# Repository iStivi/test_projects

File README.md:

Eagle project files for breakout and testing boards.

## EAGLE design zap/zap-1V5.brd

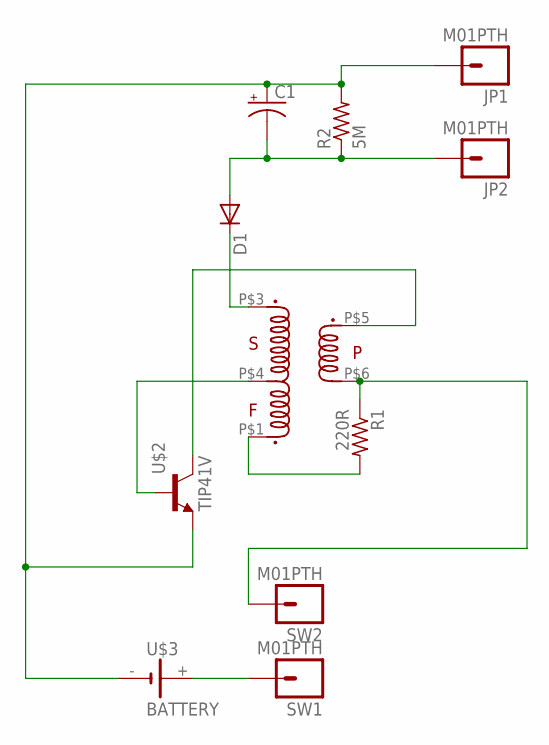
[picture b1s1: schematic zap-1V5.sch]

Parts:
C1: CAPACITOR_POL; E5-10,5-SIDE
D1: DIODEPTH; DIODE-1N4001
JP1, JP2: M01PTH; 1X01
R1: 220R; 0207/2V
R2: 5M; 0207/7
SW1, SW2: M01PTH; 1X01
U$1: XFT-FLYBACK3V; XFT-FLYBACK
U$2: TIP41V; TO220V
U$3: BATTERY; A90

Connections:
unnamed: C1.P$1 (+), JP1.1, R2.2, U$2.3 (E), U$3.-
unnamed: C1.P$2 (-), D1.A, JP2.1, R2.1
unnamed: D1.C, U$1.P$3 (P$1.S)
unnamed: R1.1, SW2.1, U$1.P$6 (P$5.P2)
unnamed: SW1.1, U$3.+
unnamed: R1.2, U$1.P$1 (P$3.F)
unnamed: U$1.P$4 (P$2.CENTRE), U$2.1 (B)
unnamed: U$1.P$5 (P$4.P1), U$2.2 (C)

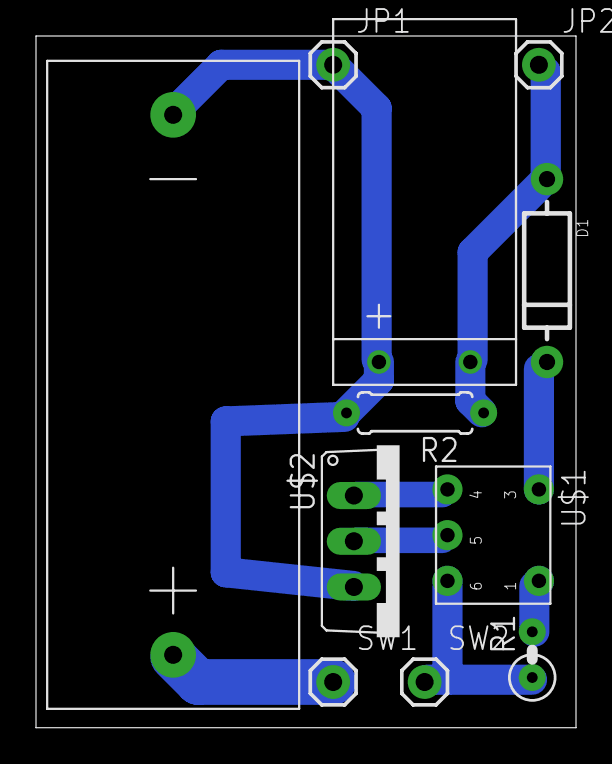
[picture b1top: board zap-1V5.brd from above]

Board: 2 copper layers, 30.0 x 38.4 mm, 11 parts (0 on the bottom side), 8 nets.

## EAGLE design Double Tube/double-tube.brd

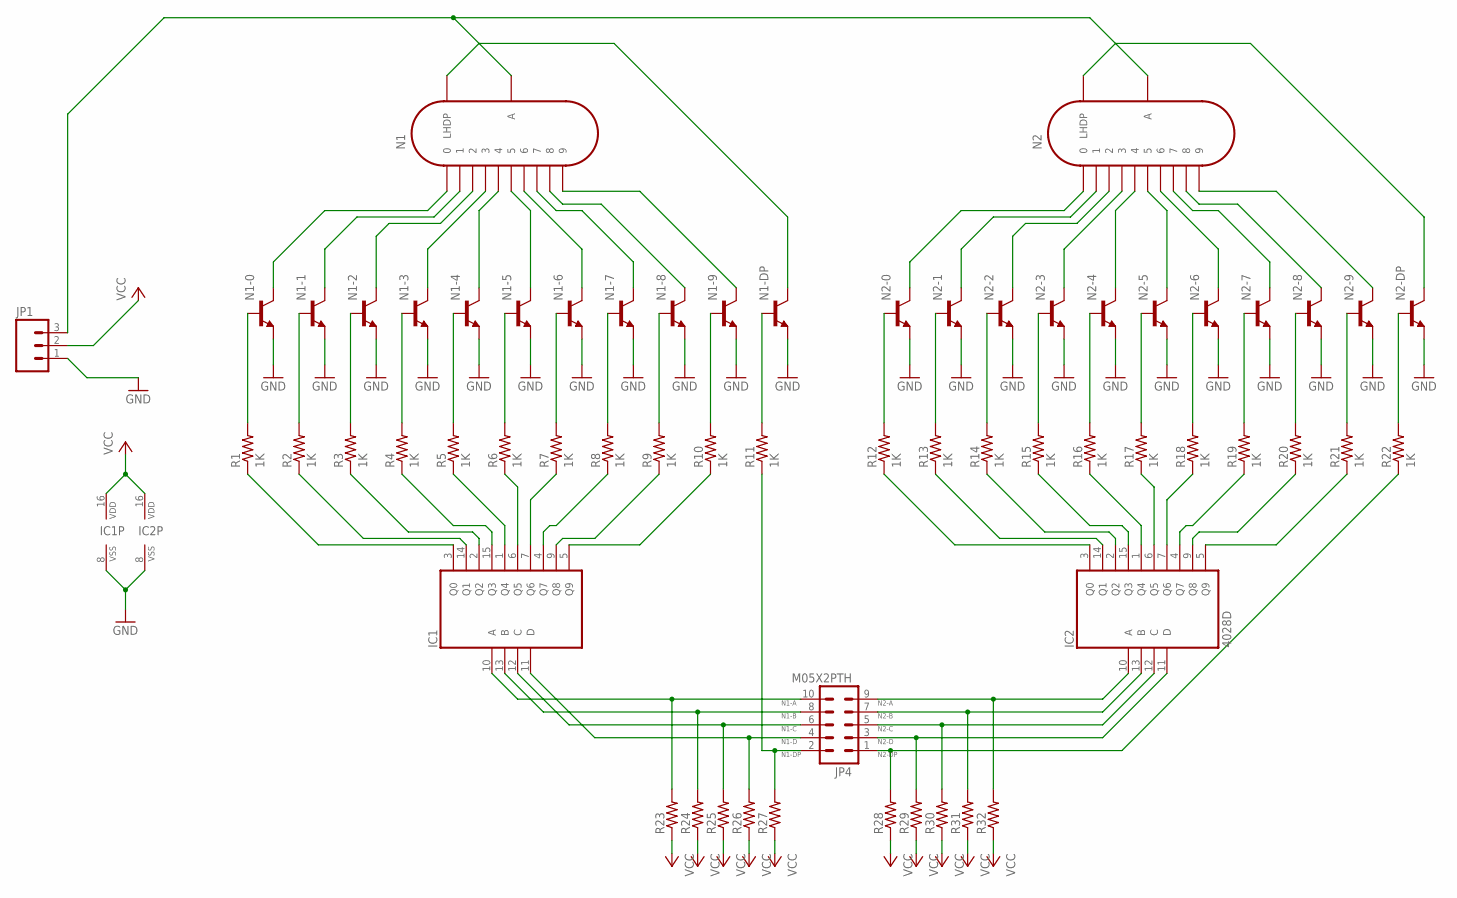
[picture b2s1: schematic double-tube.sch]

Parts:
IC1, IC2: 4028D; SO16
JP1: M03PTH; 1X03
JP4: M05X2PTH; AVR_ICSP
N1, N2: IN-12B; IN-12
N1-0, N1-1, N1-2, N1-3, N1-4, N1-5, N1-6, N1-7, N1-8, N1-9, N1-DP, N2-0, N2-1, N2-2, N2-3, N2-4, N2-5, N2-6, N2-7, N2-8, N2-9, N2-DP: NPN_SMD; SOT-23
R1, R2, R3, R4, R5, R6, R7, R8, R9, R10, R11, R12, R13, R14, R15, R16, R17, R18, R19, R20, R21, R22: 1K; R0603
R23, R24, R25, R26, R27, R28, R29, R30, R31, R32: RESISTORR0603; R0603

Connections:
180V: JP1.3, N1.A, N2.A
N1-A: IC1.10 (A), JP4.10, R23.2
N1-B: IC1.13 (B), JP4.8, R24.2
N1-C: IC1.12 (C), JP4.6, R25.2
N1-D: IC1.11 (D), JP4.4, R26.2
N1-DP: JP4.2, R11.1, R27.2
N2-0: N2.0, N2-0.3 (C)
N2-A: IC2.10 (A), JP4.9, R32.2
N2-B: IC2.13 (B), JP4.7, R31.2
N2-C: IC2.12 (C), JP4.5, R30.2
N2-D: IC2.11 (D), JP4.3, R29.2
N2-DP: JP4.1, R22.1, R28.2
unnamed: N1.0, N1-0.3 (C)
unnamed: N1.1, N1-1.3 (C)
unnamed: N1.2, N1-2.3 (C)
unnamed: N1.3, N1-3.3 (C)
unnamed: N1.4, N1-4.3 (C)
unnamed: N1.9, N1-9.3 (C)
unnamed: N1.8, N1-8.3 (C)
unnamed: N1.7, N1-7.3 (C)
unnamed: N1.6, N1-6.3 (C)
unnamed: N1.5, N1-5.3 (C)
unnamed: N1.LHDP, N1-DP.3 (C)
unnamed: N1-0.1 (B), R1.2
unnamed: N1-1.1 (B), R2.2
unnamed: N1-2.1 (B), R3.2
unnamed: N1-3.1 (B), R4.2
unnamed: N1-4.1 (B), R5.2
unnamed: N1-5.1 (B), R6.2
unnamed: N1-9.1 (B), R10.2
unnamed: N1-6.1 (B), R7.2
unnamed: N1-7.1 (B), R8.2
unnamed: N1-8.1 (B), R9.2
unnamed: IC1.3 (Q0), R1.1
unnamed: IC1.14 (Q1), R2.1
unnamed: N1-DP.1 (B), R11.2
unnamed: IC1.2 (Q2), R3.1
unnamed: N2.1, N2-1.3 (C)
unnamed: N2.2, N2-2.3 (C)
unnamed: N2.3, N2-3.3 (C)
unnamed: N2.4, N2-4.3 (C)
unnamed: N2.9, N2-9.3 (C)
unnamed: N2.8, N2-8.3 (C)
unnamed: N2.7, N2-7.3 (C)
unnamed: N2.6, N2-6.3 (C)
unnamed: N2.5, N2-5.3 (C)
unnamed: N2.LHDP, N2-DP.3 (C)
unnamed: N2-0.1 (B), R12.2
unnamed: N2-1.1 (B), R13.2
unnamed: N2-2.1 (B), R14.2
unnamed: N2-3.1 (B), R15.2
unnamed: N2-4.1 (B), R16.2
unnamed: N2-5.1 (B), R17.2
unnamed: N2-9.1 (B), R21.2
unnamed: N2-6.1 (B), R18.2
unnamed: N2-7.1 (B), R19.2
unnamed: N2-8.1 (B), R20.2
unnamed: IC1.15 (Q3), R4.1
unnamed: N2-DP.1 (B), R22.2
unnamed: IC1.1 (Q4), R5.1
unnamed: IC1.6 (Q5), R6.1
unnamed: IC1.7 (Q6), R7.1
unnamed: IC1.5 (Q9), R10.1
unnamed: IC1.9 (Q8), R9.1
unnamed: IC1.4 (Q7), R8.1
unnamed: IC2.3 (Q0), R12.1
unnamed: IC2.14 (Q1), R13.1
unnamed: IC2.2 (Q2), R14.1
unnamed: IC2.15 (Q3), R15.1
unnamed: IC2.1 (Q4), R16.1
unnamed: IC2.6 (Q5), R17.1
unnamed: IC2.7 (Q6), R18.1
unnamed: IC2.5 (Q9), R21.1
unnamed: IC2.9 (Q8), R20.1
unnamed: IC2.4 (Q7), R19.1

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
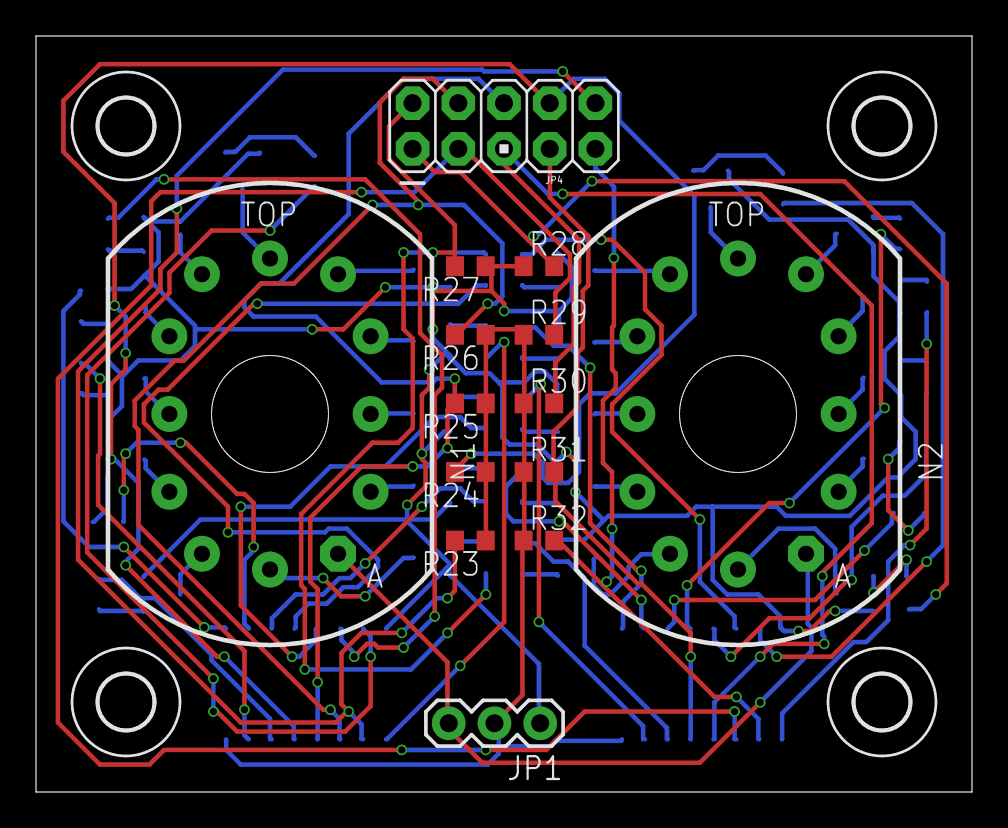
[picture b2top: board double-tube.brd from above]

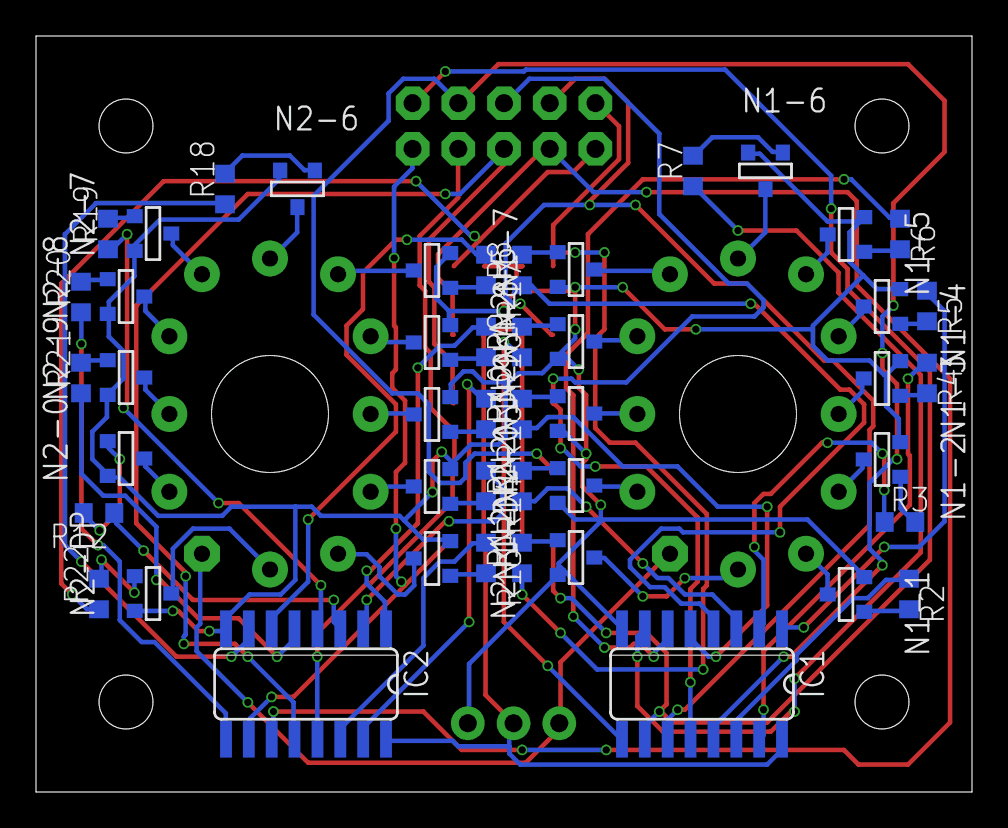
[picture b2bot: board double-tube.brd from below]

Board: 2 copper layers, 52.0 x 42.0 mm, 66 parts (47 on the bottom side), 77 nets.

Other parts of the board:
U$1: BUZZBOY-SILK
U$2, U$3, U$4, U$5: 3,0-SMALL
U$6: BUZZBOY-SILK-BOTTOM

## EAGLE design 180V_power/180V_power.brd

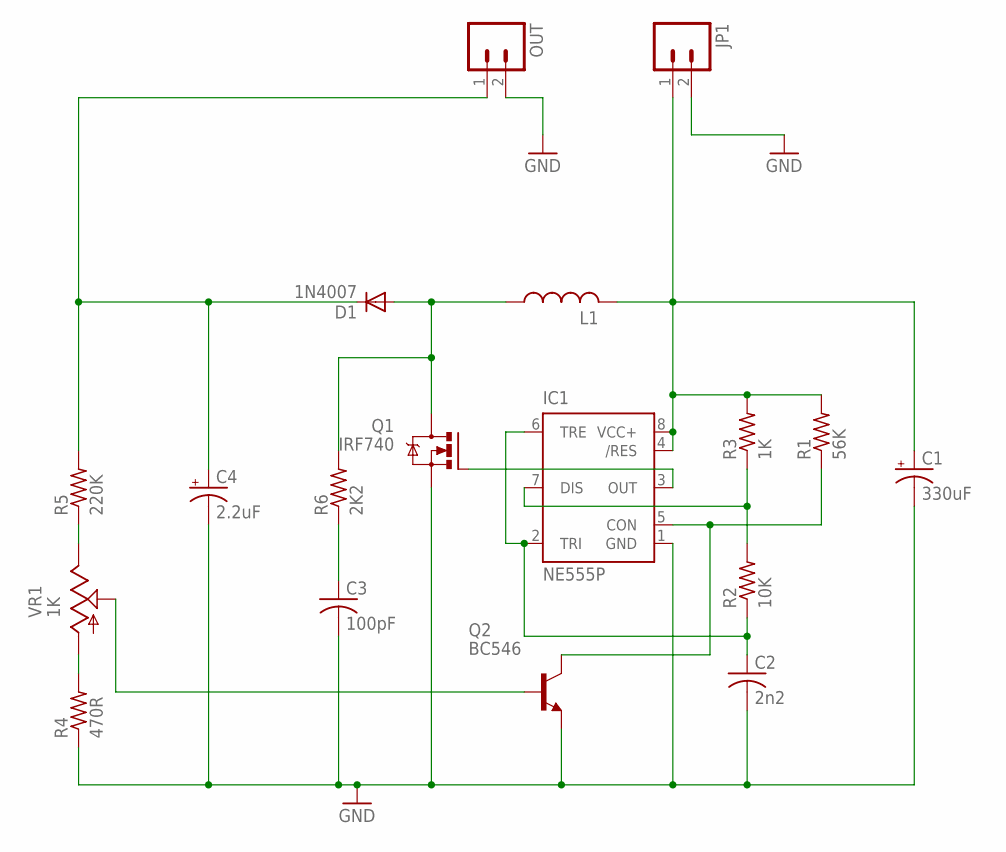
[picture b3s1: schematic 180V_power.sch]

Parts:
C1: 330uF; E5-10,5
C2: 2n2; C050-025X075
C3: 100pF; C050-025X075
C4: 2.2uF; E3,5-8
D1: 1N4007; DIODE-1N4001
IC1: NE555P; DIL08
JP1: M023.5MM; SCREWTERMINAL-3.5MM-2
L1: INDUCTOR; RBL0712
OUT: M023.5MM; SCREWTERMINAL-3.5MM-2
Q1: IRF740; TO220BV
Q2: BC546; TO92-EBC
R1: 56K; 0207/10
R2: 10K; 0207/10
R3: 1K; 0207/10
R4: 470R; 0207/10
R5: 220K; 0207/10
R6: 2K2; 0207/10
VR1: 1K; CA6V

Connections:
GND: C1.-, C2.2, C3.2, C4.-, IC1.1 (GND), JP1.2, OUT.2, Q1.S, Q2.E, R4.1
unnamed: IC1.3 (OUT), Q1.G
unnamed: C3.1, R6.1
unnamed: IC1.5 (CON), Q2.C, R1.1
unnamed: IC1.7 (DIS), R2.2, R3.1
unnamed: C2.1, IC1.2 (TRI), IC1.6 (TRE), R2.1
unnamed: D1.A, L1.P$1 (1), Q1.D, R6.2
unnamed: C4.+, D1.C, OUT.1, R5.2
unnamed: R5.1, VR1.E
unnamed: R4.2, VR1.A
unnamed: Q2.B, VR1.S
unnamed: C1.+, IC1.4 (/RES), IC1.8 (VCC+), JP1.1, L1.P$2 (2), R1.2, R3.2

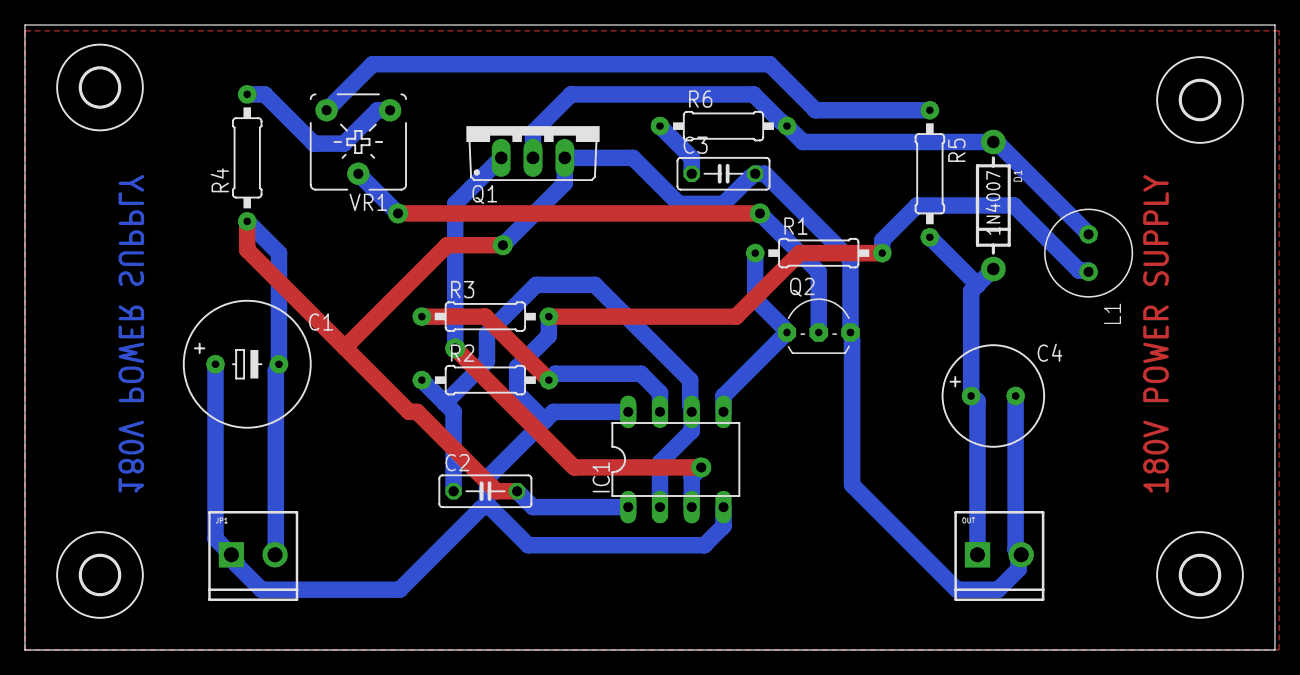
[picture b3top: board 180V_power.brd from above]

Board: 2 copper layers, 100.0 x 50.0 mm, 22 parts (0 on the bottom side), 12 nets.

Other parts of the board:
U$1, U$2, U$3, U$4: 3,0

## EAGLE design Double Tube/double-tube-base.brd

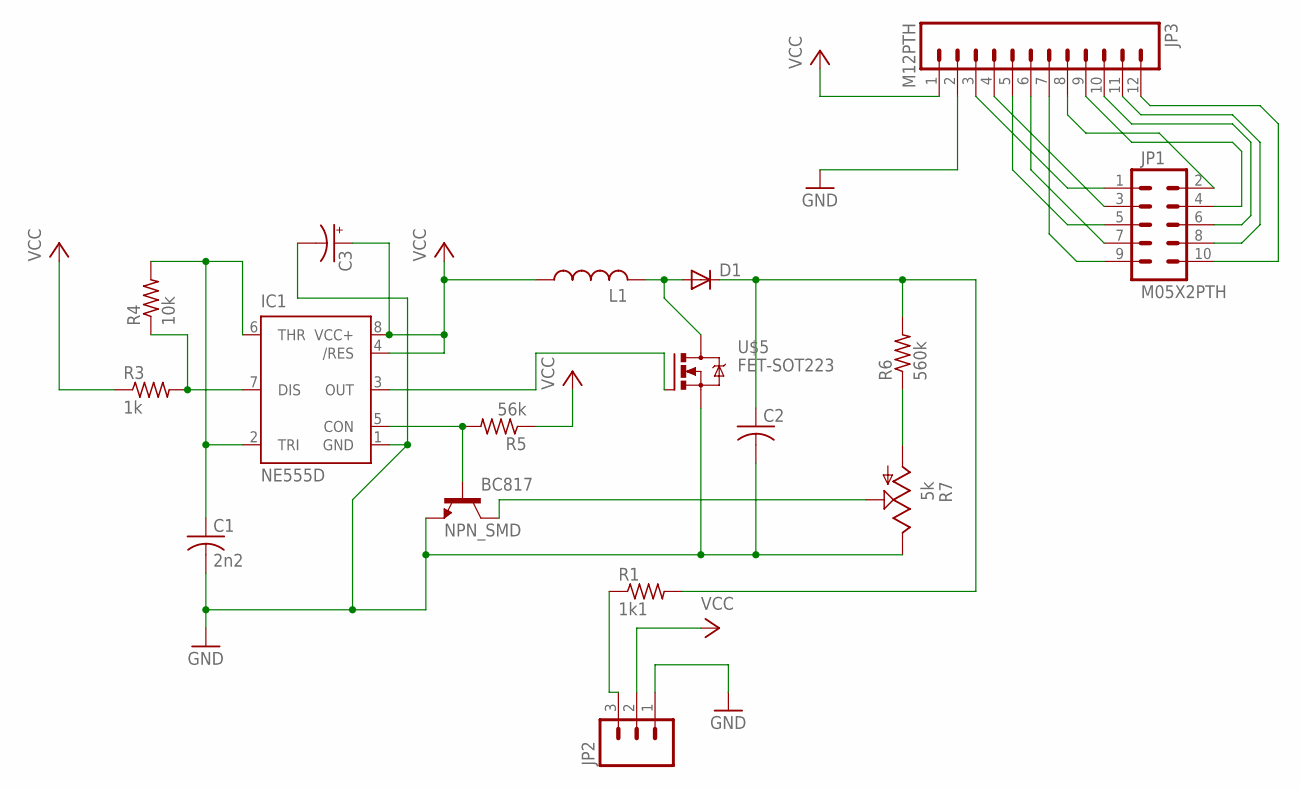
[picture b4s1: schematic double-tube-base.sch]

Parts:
BC817: NPN_SMD; SOT-23
C1: 2n2; C0603K
C2: CAPACITORC1812K; C1812K
C3: CAPACITOR_POLSMCD; SMC_D
D1: DIODESMA; SMA-DIODE
IC1: NE555D; SO08
JP1: M05X2PTH; AVR_ICSP
JP2: M03PTH; 1X03
JP3: M12PTH; 1X12
L1: INDUCTORSMD-10MM; SMD-10MM
R1: 1k1; R1206
R3: 1k; R0603
R4: 10k; R0603
R5: 56k; R0603
R6: 560k; R1206
R7: 5k; TRIM-EVM2N
U$5: FET-SOT223; SOT-223

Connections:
GND: BC817.2 (E), C1.2, C2.2, C3.-, IC1.1 (GND), JP2.1, JP3.2, R7.P$3 (E), U$5.3 (S)
unnamed: IC1.7 (DIS), R3.2, R4.1
unnamed: C1.1, IC1.2 (TRI), IC1.6 (THR), R4.2
unnamed: BC817.1 (B), IC1.5 (CON), R5.2
unnamed: D1.A, L1.P$2 (2), U$5.2 (D), U$5.4 (D)
unnamed: C2.1, D1.C, R1.2, R6.2
unnamed: BC817.3 (C), R7.P$2 (S)
unnamed: R6.1, R7.P$1 (A)
unnamed: IC1.3 (OUT), U$5.1 (G)
unnamed: JP2.3, R1.1
unnamed: JP1.1, JP3.3
unnamed: JP1.3, JP3.4
unnamed: JP1.5, JP3.5
unnamed: JP1.7, JP3.6
unnamed: JP1.9, JP3.7
unnamed: JP1.2, JP3.8
unnamed: JP1.4, JP3.9
unnamed: JP1.6, JP3.10
unnamed: JP1.8, JP3.11
unnamed: JP1.10, JP3.12
VCC: C3.+, IC1.4 (/RES), IC1.8 (VCC+), JP2.2, JP3.1, L1.P$1 (1), R3.1, R5.1

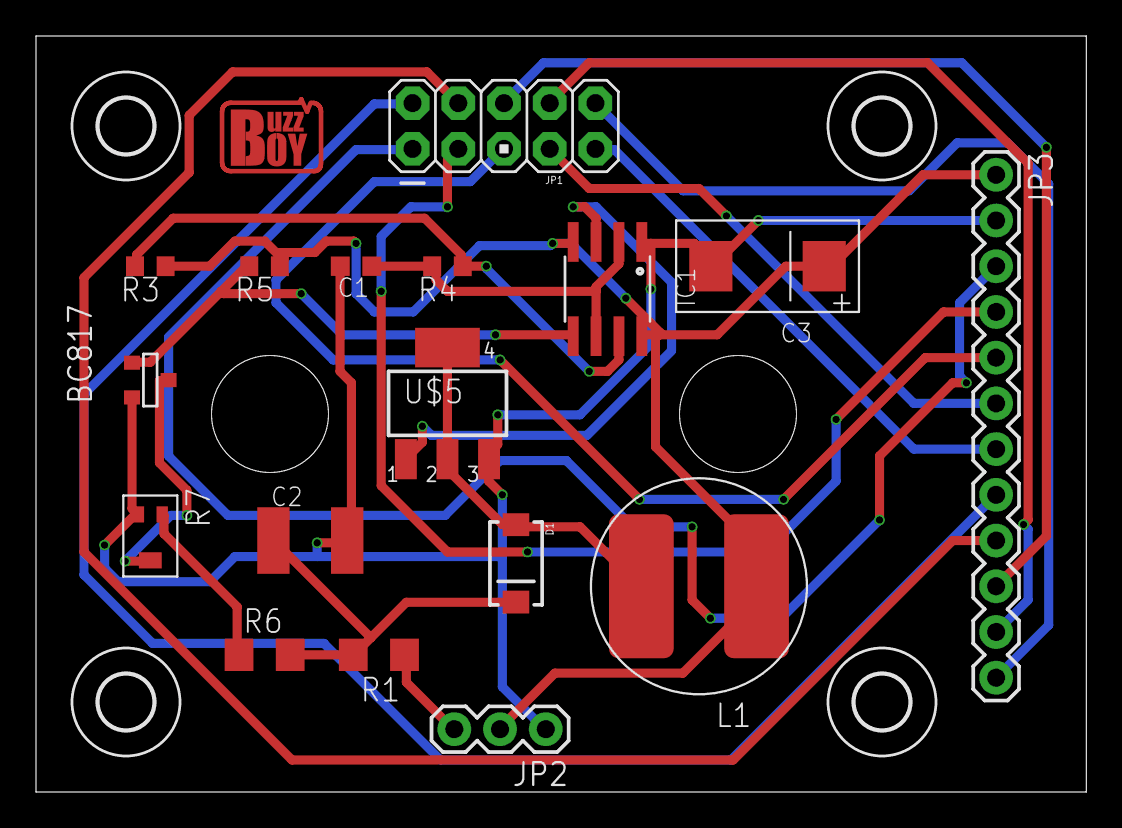
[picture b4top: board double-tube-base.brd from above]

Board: 2 copper layers, 58.4 x 42.0 mm, 23 parts (1 on the bottom side), 21 nets.

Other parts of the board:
U$1, U$2, U$3, U$4: 3,0-SMALL
U$6: BUZZBOY
U$7: BUZZBOY-SILK-BOTTOM

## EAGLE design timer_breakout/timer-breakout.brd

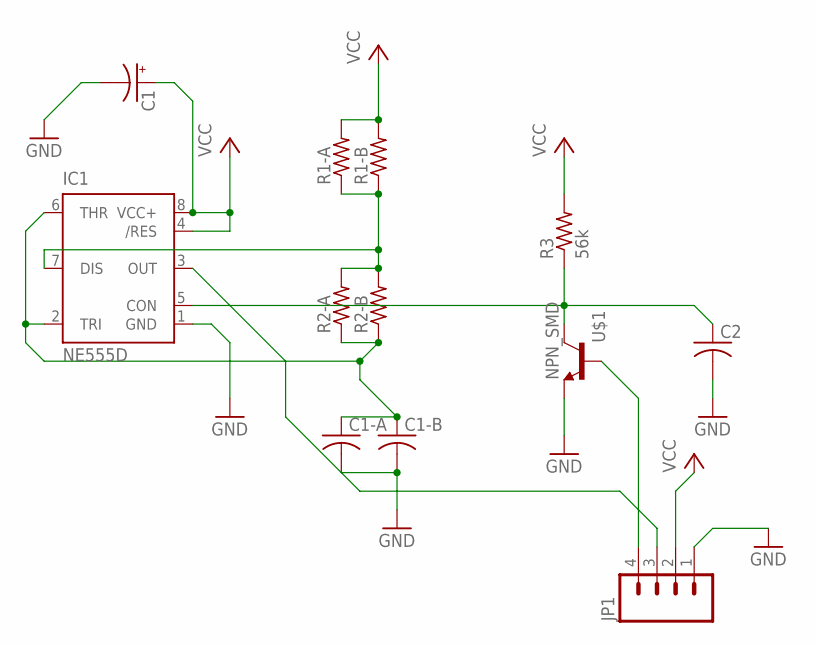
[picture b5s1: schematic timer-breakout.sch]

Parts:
C1: CAPACITOR_POLSMCD; SMC_D
C1-A, C2: CAPACITORC1206K; C1206K
C1-B: CAPACITORC0805K; C0805K
IC1: NE555D; SO08
JP1: M04PTH; 1X04
R1-A, R2-A: RESISTORR1206; R1206
R1-B, R2-B: RESISTORR0805; R0805
R3: 56k; R0805
U$1: NPN_SMD; SOT-23

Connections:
GND: C1.-, C1-A.2, C1-B.2, C2.2, IC1.1 (GND), JP1.1, U$1.2 (E)
unnamed: C1-A.1, C1-B.1, IC1.2 (TRI), IC1.6 (THR), R2-A.1, R2-B.1
unnamed: C2.1, IC1.5 (CON), R3.1, U$1.3 (C)
unnamed: JP1.4, U$1.1 (B)
unnamed: IC1.7 (DIS), R1-A.1, R1-B.1, R2-A.2, R2-B.2
unnamed: IC1.3 (OUT), JP1.3
VCC: C1.+, IC1.4 (/RES), IC1.8 (VCC+), JP1.2, R1-A.2, R1-B.2, R3.2

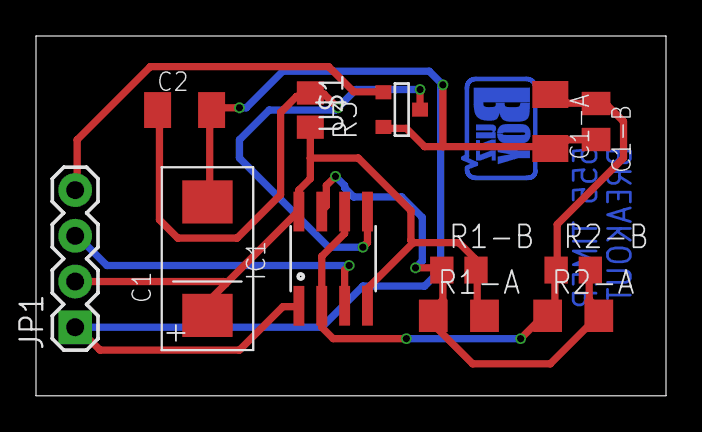
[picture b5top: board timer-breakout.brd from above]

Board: 2 copper layers, 35.0 x 20.0 mm, 14 parts (1 on the bottom side), 7 nets.

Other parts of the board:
U$2: BUZZBOY-SILK
U$3: BUZZBOY

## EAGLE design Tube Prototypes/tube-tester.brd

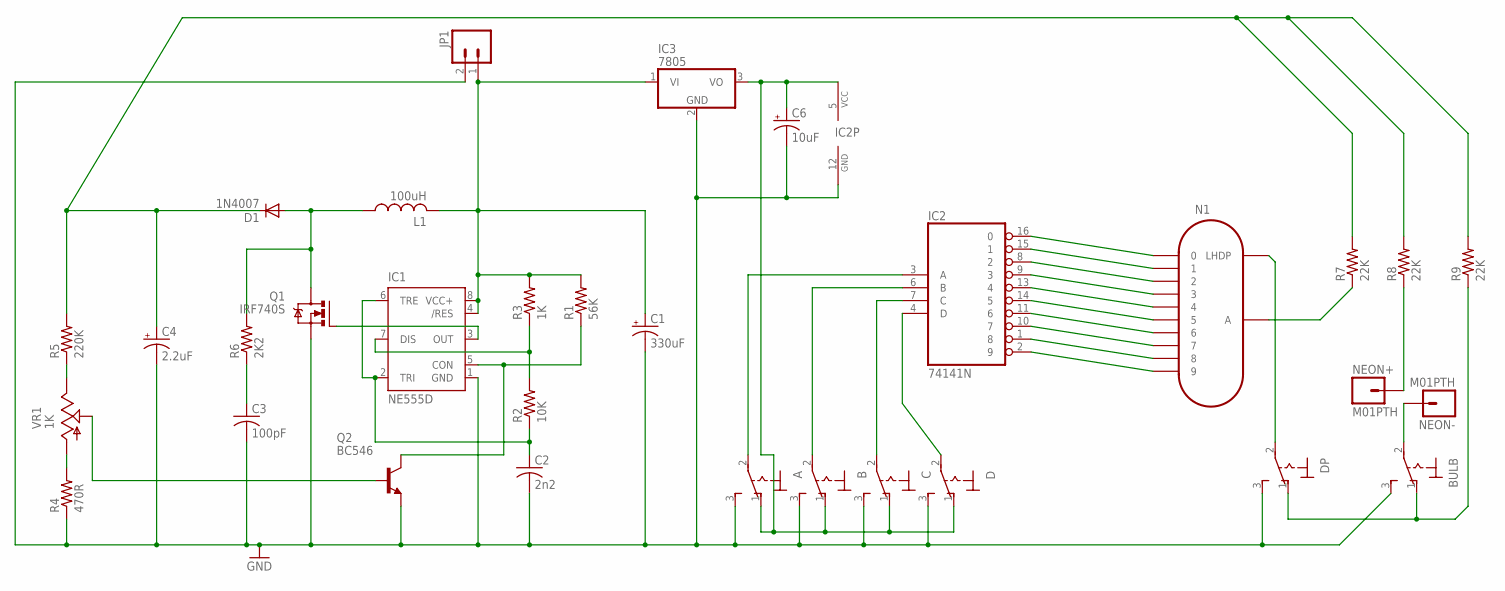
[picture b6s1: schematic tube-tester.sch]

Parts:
A: 320-916
B: 320-916
BULB: 320-916
C: 320-916
C1: 330uF; E5-10,5
C2: 2n2; C1206K
C3: 100pF; C1206K
C4: 2.2uF; E3,5-8
C6: 10uF; E2-5
D: 320-916
D1: 1N4007; SMA-DIODE
DP: 320-916
IC1: NE555D; SO08
IC2: 74141N; DIL16
IC3: 7805; TO220H
JP1: M023.5MM; SCREWTERMINAL-3.5MM-2
L1: 100uH; 0207/10
N1: IN-12B; IN-12
NEON+: M01PTH; 1X01
NEON-: M01PTH; 1X01
Q1: IRF740S; TO263
Q2: BC546; TO92-EBC
R1: 56K; R1206
R2: 10K; R1206
R3: 1K; R1206
R4: 470R; 0207/10
R5: 220K; 0207/10
R6: 2K2; R1206
R7, R8, R9: 22K; 0207/10
VR1: 1K; CA6V

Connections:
GND: A.3 (S), B.3 (S), BULB.3 (S), C.3 (S), C1.-, C2.2, C3.2, C4.-, C6.-, D.3 (S), DP.3 (S), IC1.1 (GND), IC2.12 (GND), IC3.2 (GND), JP1.2, Q1.2 (S), Q2.E, R4.1
unnamed: IC1.3 (OUT), Q1.1 (G)
unnamed: C3.1, R6.1
unnamed: IC1.5 (CON), Q2.C, R1.1
unnamed: IC1.7 (DIS), R2.2, R3.1
unnamed: C2.1, IC1.2 (TRI), IC1.6 (TRE), R2.1
unnamed: D1.A, L1.1, Q1.3 (D), R6.2
unnamed: C4.+, D1.C, R5.2, R7.2, R8.2, R9.2
unnamed: R5.1, VR1.E
unnamed: R4.2, VR1.A
unnamed: Q2.B, VR1.S
unnamed: IC2.15 (1), N1.1
unnamed: IC2.8 (2), N1.2
unnamed: IC2.9 (3), N1.3
unnamed: IC2.13 (4), N1.4
unnamed: IC2.14 (5), N1.5
unnamed: IC2.11 (6), N1.6
unnamed: IC2.10 (7), N1.7
unnamed: IC2.1 (8), N1.8
unnamed: IC2.2 (9), N1.9
unnamed: IC2.16 (0), N1.0
unnamed: N1.A, R7.1
unnamed: A.2, IC2.3 (A)
unnamed: B.2, IC2.6 (B)
unnamed: C.2, IC2.7 (C)
unnamed: D.2, IC2.4 (D)
unnamed: C1.+, IC1.4 (/RES), IC1.8 (VCC+), IC3.1 (VI), JP1.1, L1.2, R1.2, R3.2
unnamed: NEON+.1, R8.1
unnamed: BULB.2, NEON-.1
unnamed: A.1 (O), B.1 (O), C.1 (O), C6.+, D.1 (O), IC2.5 (VCC), IC3.3 (VO)
unnamed: DP.2, N1.LHDP
unnamed: BULB.1 (O), DP.1 (O), R9.1

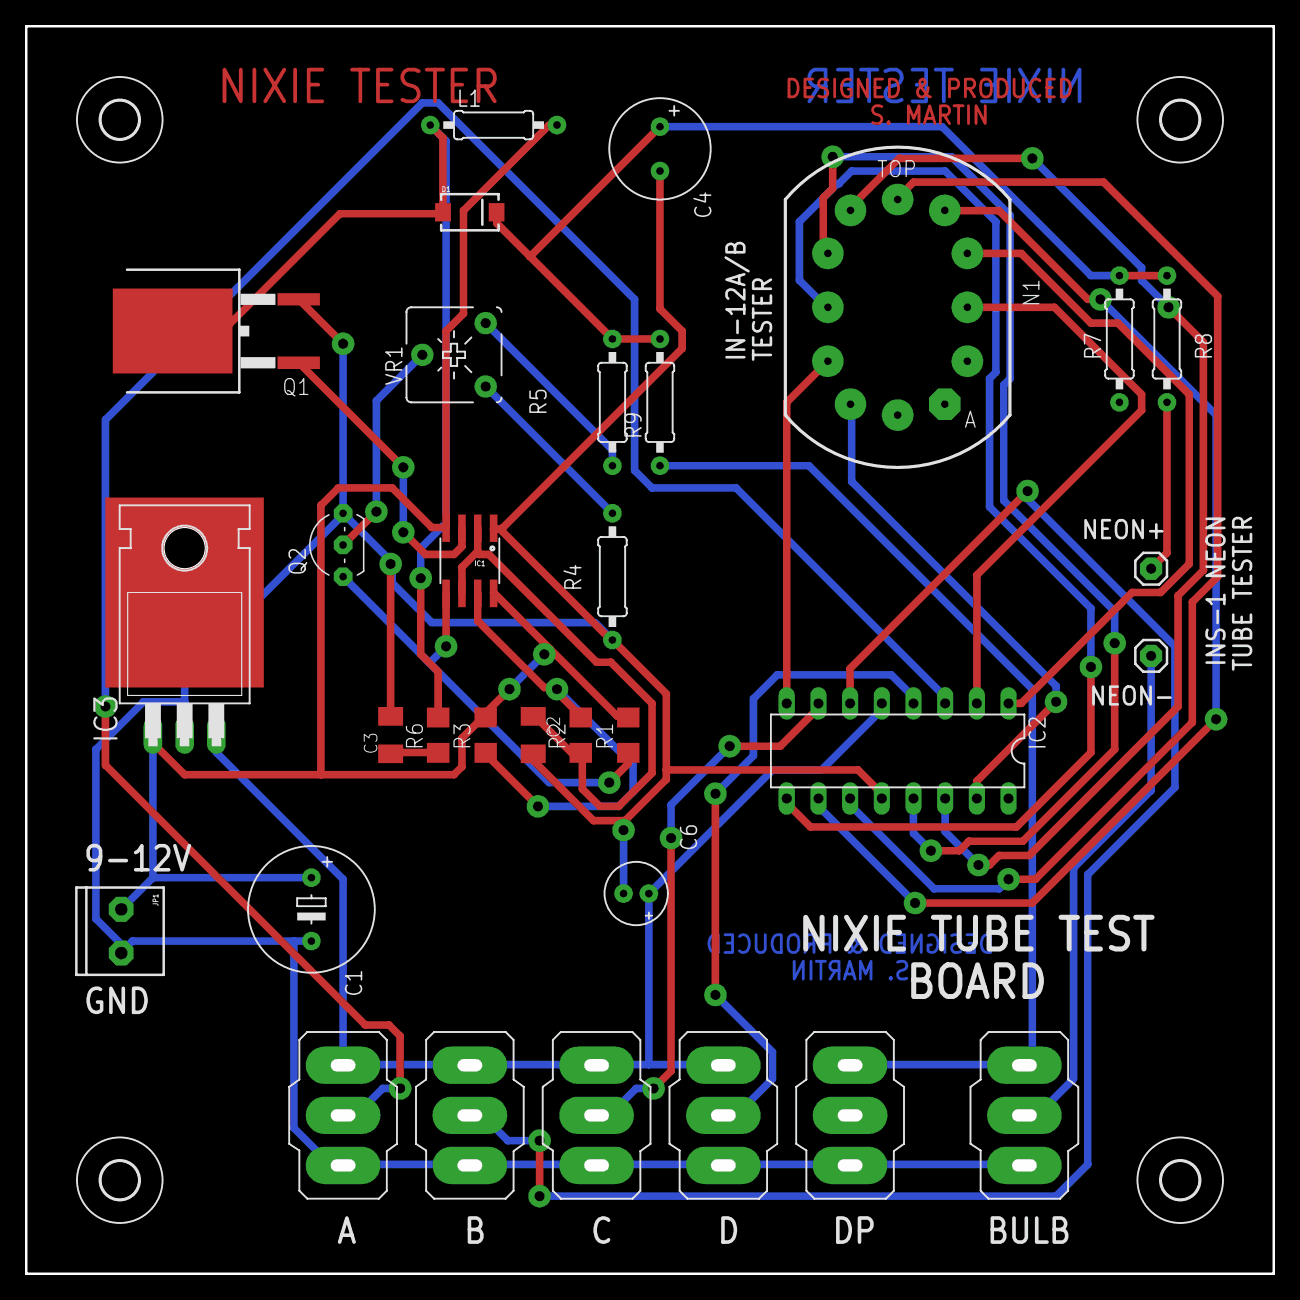
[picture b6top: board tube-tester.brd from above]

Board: 2 copper layers, 100.0 x 100.0 mm, 36 parts (0 on the bottom side), 32 nets.

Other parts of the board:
U$1, U$2, U$3, U$4: 3,0

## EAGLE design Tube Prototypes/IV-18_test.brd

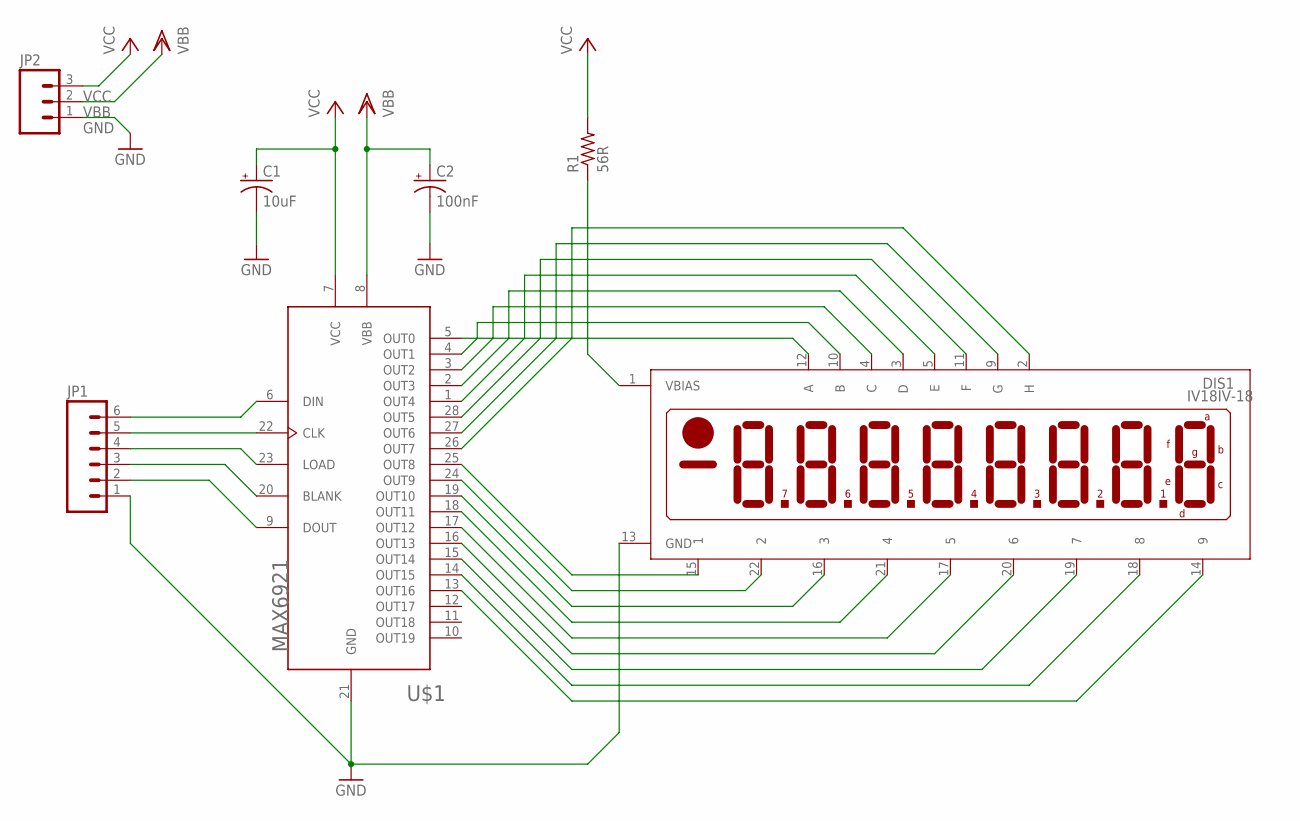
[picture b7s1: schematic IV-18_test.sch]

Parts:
C1: 10uF; E2-5
C2: 100nF; E2-5
DIS1: IV18IV-18; IV-18
JP1: M06SIP; 1X06
JP2: M03PTH; 1X03
R1: 56R; 0207/10
U$1: MAX6921AUI; TSSOP28

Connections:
GND: C1.-, C2.-, DIS1.13 (GND), JP1.1, JP2.1, U$1.21 (GND)
unnamed: DIS1.12 (A), U$1.5 (OUT0)
unnamed: DIS1.10 (B), U$1.4 (OUT1)
unnamed: DIS1.4 (C), U$1.3 (OUT2)
unnamed: DIS1.3 (D), U$1.2 (OUT3)
unnamed: DIS1.5 (E), U$1.1 (OUT4)
unnamed: DIS1.11 (F), U$1.28 (OUT5)
unnamed: DIS1.9 (G), U$1.27 (OUT6)
unnamed: DIS1.2 (H), U$1.26 (OUT7)
unnamed: DIS1.15 (1), U$1.25 (OUT8)
unnamed: DIS1.22 (2), U$1.24 (OUT9)
unnamed: DIS1.16 (3), U$1.19 (OUT10)
unnamed: DIS1.21 (4), U$1.18 (OUT11)
unnamed: DIS1.17 (5), U$1.17 (OUT12)
unnamed: DIS1.20 (6), U$1.16 (OUT13)
unnamed: DIS1.19 (7), U$1.15 (OUT14)
unnamed: DIS1.18 (8), U$1.14 (OUT15)
unnamed: DIS1.14 (9), U$1.13 (OUT16)
unnamed: JP1.6, U$1.6 (DIN)
unnamed: JP1.5, U$1.22 (CLK)
unnamed: JP1.4, U$1.23 (LOAD)
unnamed: JP1.3, U$1.20 (BLANK)
unnamed: JP1.2, U$1.9 (DOUT)
VBB: C2.+, JP2.2, U$1.8 (VBB)
VBIAS: DIS1.1 (VBIAS), R1.1
VCC: C1.+, JP2.3, R1.2, U$1.7 (VCC)

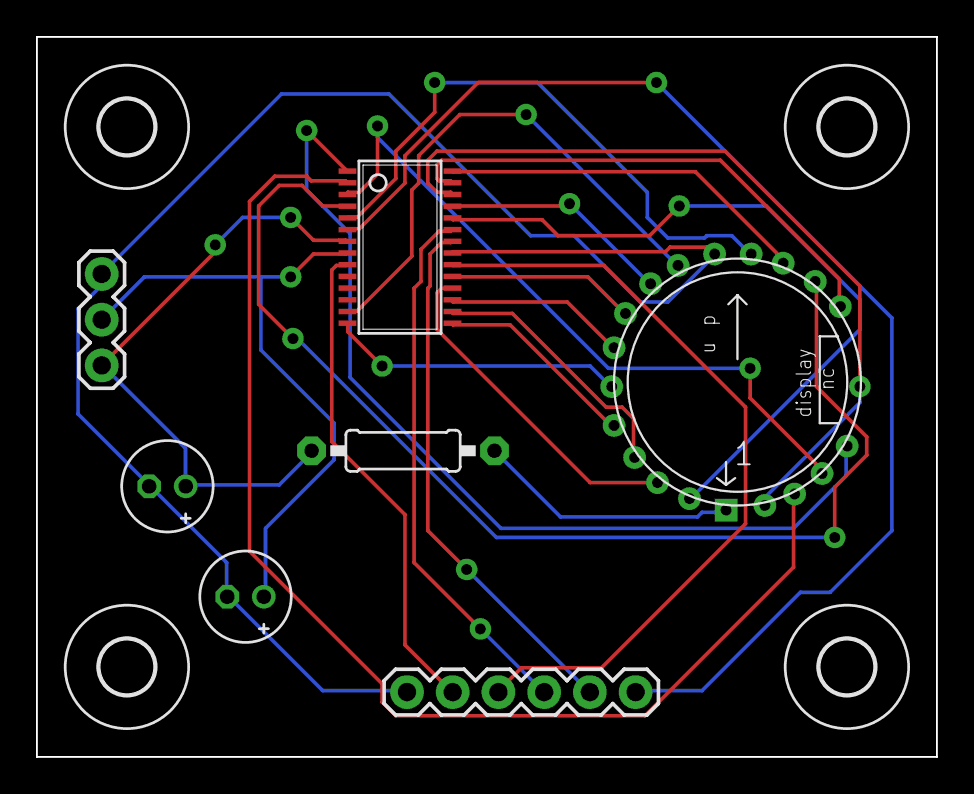
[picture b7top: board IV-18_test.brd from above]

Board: 2 copper layers, 50.0 x 40.0 mm, 11 parts (0 on the bottom side), 26 nets.

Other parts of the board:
U$4, U$5, U$6, U$7: 3,0

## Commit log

2013-07-04 update ignore
2013-07-04 readme
2013-07-04 breakout board update
2013-07-05 finished
2013-07-05 minor size change
2013-07-05 added cam jobs
2013-07-07 made board for IV-18 teser
2013-07-07 update IV-18 tester
2013-07-07 tube tester board
2013-07-08 drills
2013-07-08 tube tester
2013-07-11 git that shit
2013-07-30 boards update
2013-08-01 update cam job file
2013-08-05 new ignore
2013-08-14 processed cam jobs
2013-08-15 new board layout for tube tester
2013-08-16 new silk screen for tube tester
2013-08-19 new tester board
2013-08-19 iv-18 board
2013-09-16 iv-18
2013-10-01 made 180V power supply
2013-10-04 update neons
2013-10-08 new 180v board
2013-10-09 new epf
2013-10-09 new 180V and tube tester
2013-10-22 new ignore
    leaves out epf file and ps and xcf files from cam process
2013-10-22 ignore fixed
2013-10-26 new boards no cu pour
2013-10-26 fixed tester
2013-12-14 started clock prototype schematic
2013-12-17 clock update
2013-12-31 tube tester redo
2014-01-05 neew
2014-01-09 new h-bridge board
2014-01-10 fixed iv-18 boardf
2014-01-10 new tube tester
2014-01-13 new stuff
2014-01-22 finished routing h-bridge board
2014-06-02 clock pulse test new
2014-06-03 prototypes processed
2014-07-31 made board smaller for production
2014-08-06 board almost final
2014-09-30 added protection diode
2014-10-01 lalala
2014-10-23 new format
2014-12-01 new ic breakout
2014-12-22 still working on 3pin breakout
2015-04-27 new prototype for dual tube board
2015-05-17 bigger hole on IN-12
2015-07-06 Update some files
2015-08-06 new simple 180 board
2015-08-31 double
2015-10-16 fix zap
2015-10-16 1.5v zap
